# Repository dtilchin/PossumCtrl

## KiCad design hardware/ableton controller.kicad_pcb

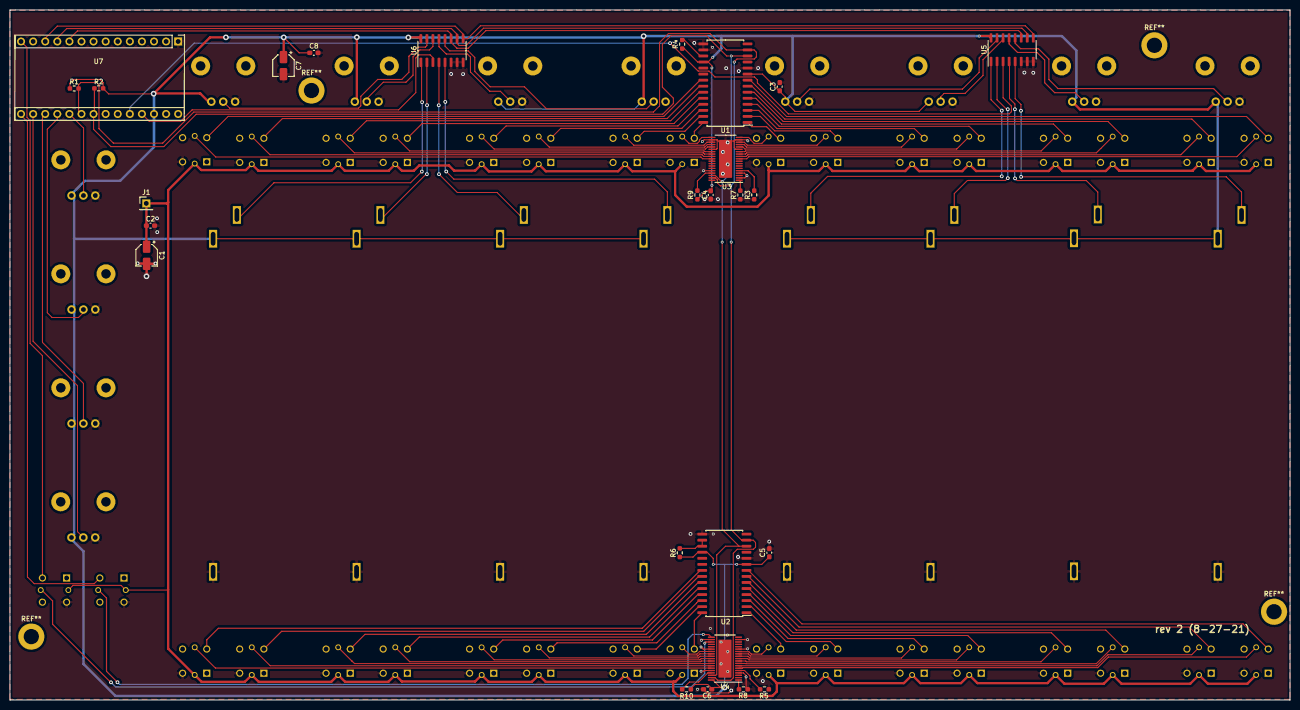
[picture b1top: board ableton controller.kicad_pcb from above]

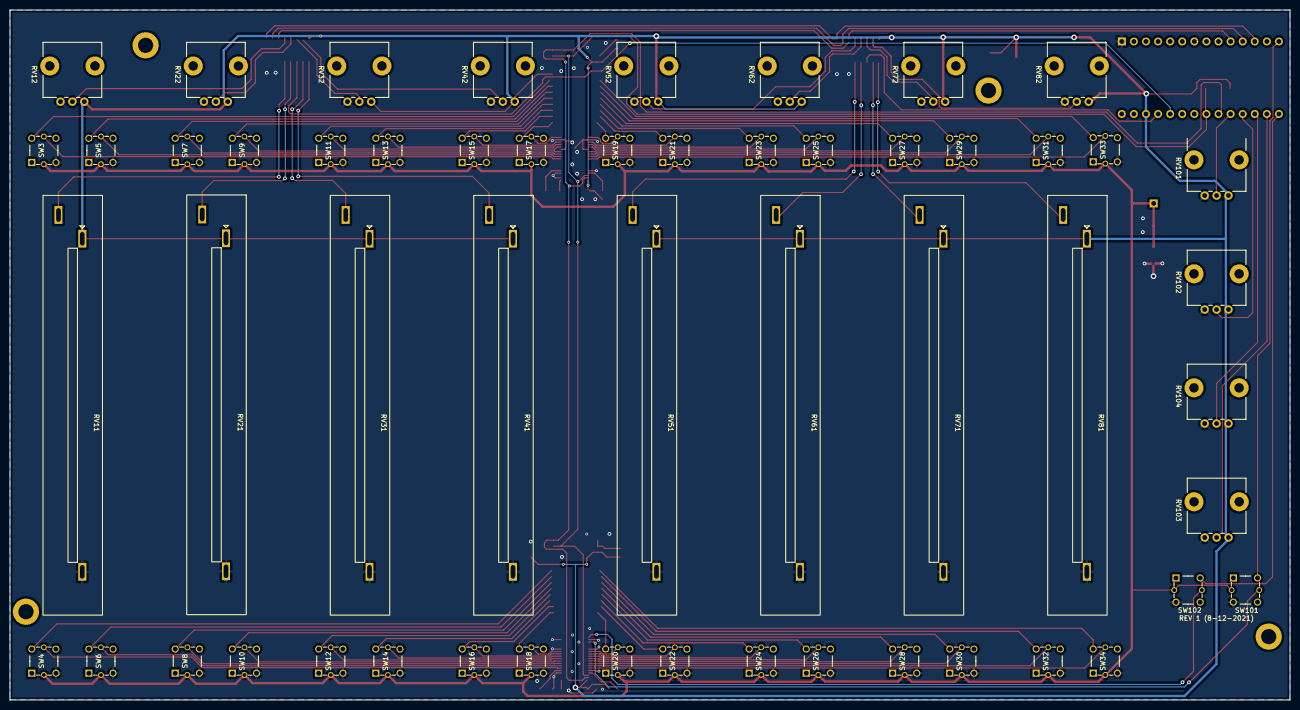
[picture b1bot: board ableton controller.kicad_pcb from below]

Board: 2 copper layers, 269.0 x 145.0 mm, 80 parts (54 on the bottom side), 106 nets.

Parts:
C1, C7: 10u; CP_Elec_4x4.5
C2, C3, C4, C5, C6, C8: 100n; C_0603_1608Metric_Pad1.08x0.95mm_HandSolder
J1: USB_header; PinHeader_1x01_P2.54mm_Vertical
R1, R2: 2k; R_0603_1608Metric_Pad0.98x0.95mm_HandSolder
R3, R4, R5, R6, R9, R10: 10k; R_0603_1608Metric_Pad0.98x0.95mm_HandSolder
R7, R8: 1k; R_0603_1608Metric_Pad0.98x0.95mm_HandSolder
RV11, RV21, RV31, RV41, RV51, RV61, RV71, RV81: R_gain; pot_slide_alpha_RA6020F
RV12, RV22, RV32, RV42, RV52, RV62, RV72, RV82: R_fx; Potentiometer_TaydaRV9312_Alpha901F_AlpsRK09L
RV101: R_fx_1; Potentiometer_TaydaRV9312_Alpha901F_AlpsRK09L
RV102: R_fx_2; Potentiometer_TaydaRV9312_Alpha901F_AlpsRK09L
RV103: R_fx_3; Potentiometer_TaydaRV9312_Alpha901F_AlpsRK09L
RV104: R_fx_4; Potentiometer_TaydaRV9312_Alpha901F_AlpsRK09L
SW3, SW7, SW11, SW15, SW19, SW23, SW27, SW31: SW_mute; Switch_button_LED_SPST_TS5_9.2mm
SW4, SW8, SW12, SW16, SW20, SW24, SW28, SW32: SW_play; Switch_button_LED_SPST_TS5_9.2mm
SW5, SW9, SW13, SW17, SW21, SW25, SW29, SW33: SW_solo; Switch_button_LED_SPST_TS5_9.2mm
SW6, SW10, SW14, SW18, SW22, SW26, SW30, SW34: SW_rec; Switch_button_LED_SPST_TS5_9.2mm
SW101: SW_m_rec; Switch_button_LED_SPST_TS5_9.2mm
SW102: SW_m_play; Switch_button_LED_SPST_TS5_9.2mm
U1, U2: MCP23017_SO; SOIC-28W_7.5x17.9mm_P1.27mm
U3, U4: PCA9956BTWY; TSSOP-38_4.4x9.7mm_P0.5mm_thermal39p
U5, U6: CD4051B; SOIC-16_3.9x9.9mm_P1.27mm
U7: Teensy-LC_sidepins; Teensy40_headers

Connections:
+5V: C1.1, C2.1, J1.1, SW3.6, SW4.6, SW5.6, SW6.6, SW7.6, SW8.6, SW9.6, SW10.6, SW11.6, SW12.6, SW13.6, SW14.6, SW15.6, SW16.6, SW17.6, SW18.6, SW19.6, SW20.6, SW21.6, SW22.6, SW23.6, SW24.6, SW25.6, SW26.6, SW27.6, SW28.6, SW29.6, SW30.6, SW31.6, SW32.6, SW33.6, SW34.6, SW101.6, SW102.6
/ADC0: U5.3 (X), U7.24 (22_A8_SCL1_PWM_Touch)
/ADC1: U6.3 (X), U7.25 (23_A9_SDA1_PWM_Touch)
/LED_MUTE_1: SW3.5, U3.10 (LED4)
/LED_MUTE_2: SW7.5, U3.12 (LED6)
/LED_MUTE_3: SW11.5, U3.15 (LED8)
/LED_MUTE_4: SW15.5, U3.17 (LED10)
/LED_MUTE_5: SW19.5, U3.20 (LED12)
/LED_MUTE_6: SW23.5, U3.23 (LED14)
/LED_MUTE_7: SW27.5, U3.26 (LED16)
/LED_MUTE_8: SW31.5, U3.28 (LED18)
/LED_PLAY: SW102.5, U4.20 (LED12)
/LED_PLAY_1: SW4.5, U4.6 (LED0)
/LED_PLAY_2: SW8.5, U4.8 (LED2)
/LED_PLAY_3: SW12.5, U4.10 (LED4)
/LED_PLAY_4: SW16.5, U4.12 (LED6)
/LED_PLAY_5: SW20.5, U4.26 (LED16)
/LED_PLAY_6: SW24.5, U4.28 (LED18)
/LED_PLAY_7: SW28.5, U4.30 (LED20)
/LED_PLAY_8: SW32.5, U4.32 (LED22)
/LED_REC: SW101.5, U4.22 (LED13)
/LED_REC_1: SW6.5, U4.7 (LED1)
/LED_REC_2: SW10.5, U4.9 (LED3)
/LED_REC_3: SW14.5, U4.11 (LED5)
/LED_REC_4: SW18.5, U4.13 (LED7)
/LED_REC_5: SW22.5, U4.27 (LED17)
/LED_REC_6: SW26.5, U4.29 (LED19)
/LED_REC_7: SW30.5, U4.31 (LED21)
/LED_REC_8: SW34.5, U4.33 (LED23)
/LED_SOLO_1: SW5.5, U3.11 (LED5)
/LED_SOLO_2: SW9.5, U3.13 (LED7)
/LED_SOLO_3: SW13.5, U3.16 (LED9)
/LED_SOLO_4: SW17.5, U3.19 (LED11)
/LED_SOLO_5: SW21.5, U3.22 (LED13)
/LED_SOLO_6: SW25.5, U3.24 (LED15)
/LED_SOLO_7: SW29.5, U3.27 (LED17)
/LED_SOLO_8: SW33.5, U3.29 (LED19)
/MUX_POT_A: U5.11 (A), U6.11 (A), U7.10 (8_TX3_MISO0)
/MUX_POT_B: U5.10 (B), U6.10 (B), U7.11 (9_RX2_PWM)
/MUX_POT_C: U5.9 (C), U6.9 (C), U7.12 (10_TX2_CS0_PWM)
/POT_FX_1: RV101.2, U7.19 (17_A3_SDA0_PWM_Touch)
/POT_FX_2: RV102.2, U7.18 (16_A2_SCL0_PWM_Touch)
/POT_FX_3: RV103.2, U7.16 (14_A0_SCK0)
/POT_FX_4: RV104.2, U7.17 (15_A1_Touch)
/POT_GAIN_1: RV11.2, U5.5 (X5)
/POT_GAIN_2: RV21.2, U5.4 (X7)
/POT_GAIN_3: RV31.2, U5.2 (X6)
/POT_GAIN_4: RV41.2, U5.1 (X4)
/POT_GAIN_5: RV51.2, U6.5 (X5)
/POT_GAIN_6: RV61.2, U6.4 (X7)
/POT_GAIN_7: RV71.2, U6.2 (X6)
/POT_GAIN_8: RV81.2, U6.1 (X4)
/POT_UTIL_1: RV12.2, U5.12 (X3)
/POT_UTIL_2: RV22.2, U5.13 (X0)
/POT_UTIL_3: RV32.2, U5.14 (X1)
/POT_UTIL_4: RV42.2, U5.15 (X2)
/POT_UTIL_5: RV52.2, U6.12 (X3)
/POT_UTIL_6: RV62.2, U6.13 (X0)
/POT_UTIL_7: RV72.2, U6.14 (X1)
/POT_UTIL_8: RV82.2, U6.15 (X2)
/SCL: R2.2, U1.12 (SCK), U2.12 (SCK), U3.36 (SCL), U4.36 (SCL), U7.21 (19_A5_SCL0_Touch)
/SDA: R1.2, U1.13 (SDA), U2.13 (SDA), U3.37 (SDA), U4.37 (SDA), U7.20 (18_A4_SDA0_Touch)
/SW_MUTE_1: SW3.2, U1.8 (GPB7)
/SW_MUTE_2: SW7.2, U1.6 (GPB5)
/SW_MUTE_3: SW11.2, U1.4 (GPB3)
/SW_MUTE_4: SW15.2, U1.2 (GPB1)
/SW_MUTE_5: SW19.2, U1.28 (GPA7)
/SW_MUTE_6: SW23.2, U1.26 (GPA5)
/SW_MUTE_7: SW27.2, U1.24 (GPA3)
/SW_MUTE_8: SW31.2, U1.22 (GPA1)
/SW_PLAY: SW102.2, U7.15 (13_LED_SCK0)
/SW_PLAY_1: SW4.2, U2.8 (GPB7)
/SW_PLAY_2: SW8.2, U2.6 (GPB5)
/SW_PLAY_3: SW12.2, U2.4 (GPB3)
/SW_PLAY_4: SW16.2, U2.2 (GPB1)
/SW_PLAY_5: SW20.2, U2.28 (GPA7)
/SW_PLAY_6: SW24.2, U2.26 (GPA5)
/SW_PLAY_7: SW28.2, U2.24 (GPA3)
/SW_PLAY_8: SW32.2, U2.22 (GPA1)
/SW_REC: SW101.2, U7.14 (12_MISO0)
/SW_REC_1: SW6.2, U2.7 (GPB6)
/SW_REC_2: SW10.2, U2.5 (GPB4)
/SW_REC_3: SW14.2, U2.3 (GPB2)
/SW_REC_4: SW18.2, U2.1 (GPB0)
/SW_REC_5: SW22.2, U2.27 (GPA6)
/SW_REC_6: SW26.2, U2.25 (GPA4)
/SW_REC_7: SW30.2, U2.23 (GPA2)
/SW_REC_8: SW34.2, U2.21 (GPA0)
/SW_SOLO_1: SW5.2, U1.7 (GPB6)
/SW_SOLO_2: SW9.2, U1.5 (GPB4)
/SW_SOLO_3: SW13.2, U1.3 (GPB2)
/SW_SOLO_4: SW17.2, U1.1 (GPB0)
/SW_SOLO_5: SW21.2, U1.27 (GPA6)
/SW_SOLO_6: SW25.2, U1.25 (GPA4)
/SW_SOLO_7: SW29.2, U1.23 (GPA2)
/SW_SOLO_8: SW33.2, U1.21 (GPA0)
GND: C1.2, C2.2, C3.2, C4.2, C5.2, C6.2, C7.2, C8.2, R3.2, R5.2, R7.2, R8.2, RV11.3, RV12.3, RV21.3, RV22.3, RV31.3, RV32.3, RV41.3, RV42.3, RV51.3, RV52.3, RV61.3, RV62.3, RV71.3, RV72.3, RV81.3, RV82.3, RV101.3, RV102.3, RV103.3, RV104.3, SW3.3, SW4.3, SW5.3, SW6.3, SW7.3, SW8.3, SW9.3, SW10.3, SW11.3, SW12.3, SW13.3, SW14.3, SW15.3, SW16.3, SW17.3, SW18.3, SW19.3, SW20.3, SW21.3, SW22.3, SW23.3, SW24.3, SW25.3, SW26.3, SW27.3, SW28.3, SW29.3, SW30.3, SW31.3, SW32.3, SW33.3, SW34.3, SW101.3, SW102.3, U1.10 (VSS), U1.15 (A0), U1.16 (A1), U2.10 (VSS), U2.15 (A0), U3.2 (AD0), U3.4 (AD2), U3.14 (VSS), U3.18 (VSS), U3.21 (VSS), U3.25 (VSS), U3.34 (VSS), U3.39 (EXP), U4.4 (AD2), U4.14 (VSS), U4.18 (VSS), U4.21 (VSS), U4.25 (VSS), U4.34 (VSS), U4.39 (EXP), U5.6 (INH), U5.7 (VEE), U5.8 (VSS), U6.6 (INH), U6.7 (VEE), U6.8 (VSS), U7.1 (GND)
unnamed: R3.1, U3.5 (~OE)
unnamed: R4.2, U1.17 (A2)
unnamed: R5.1, U4.5 (~OE)
unnamed: R6.2, U2.16 (A1), U2.17 (A2)
unnamed: R7.1, U3.1 (REXT)
unnamed: R8.1, U4.1 (REXT)
unnamed: R9.2, U3.35 (~RESET)
unnamed: R10.2, U4.35 (~RESET)
VCC: C3.1, C4.1, C5.1, C6.1, C7.1, C8.1, R1.1, R2.1, R4.1, R6.1, R9.1, R10.1, RV11.1, RV12.1, RV21.1, RV22.1, RV31.1, RV32.1, RV41.1, RV42.1, RV51.1, RV52.1, RV61.1, RV62.1, RV71.1, RV72.1, RV81.1, RV82.1, RV101.1, RV102.1, RV103.1, RV104.1, U1.9 (VDD), U1.18 (~RESET~), U2.9 (VDD), U2.18 (~RESET~), U3.38 (VDD), U4.38 (VDD), U5.16 (VDD), U6.16 (VDD), U7.26 (3.3V)

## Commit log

2021-08-27 Initial commit. Works ok :)
2021-08-27 PCB: Rev2. REXT and RESET pullups. 5v caps. Rerouting/cleanup.
2021-08-28 Disabled LEDs based on track count
    + misc things such as adjusting the current
2021-08-29 PCB: New panel, layout cleanup, maybe some fixes too?
2021-09-01 LED brightness varies by color
2021-09-01 Joystick added
2021-10-04 Live: start/stop work more good
2021-10-04 PCB: Tweaks? Fixes?
2021-10-04 Brightness adjustments
